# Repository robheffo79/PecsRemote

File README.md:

# PECS Remote

A Control and Administration platform for a PECS (Picture Exchange Communication System) based Remote Control system for people with ASD (Autism Spectrum Disorder) or other learning difficulties.

## Description

This software is being developed to accompany the hardware platform described at [hackaday.io](https://hackaday.io/project/166070-pecs-remote-control).
The aim is to create an integrated platform to display a pictographic representation of choices available to the user, and allow them to choose via a simple touch of the screen.
The platform needs to be reliable, rugged, simple to use, simple to administer, and secure.

## Authors

[Robert Heffernan](https://hackaday.io/RobHeffo)

## Version History

* 0.1
    * Initial Release

## License

This project is licensed under the MIT License - see the LICENSE.md file for details

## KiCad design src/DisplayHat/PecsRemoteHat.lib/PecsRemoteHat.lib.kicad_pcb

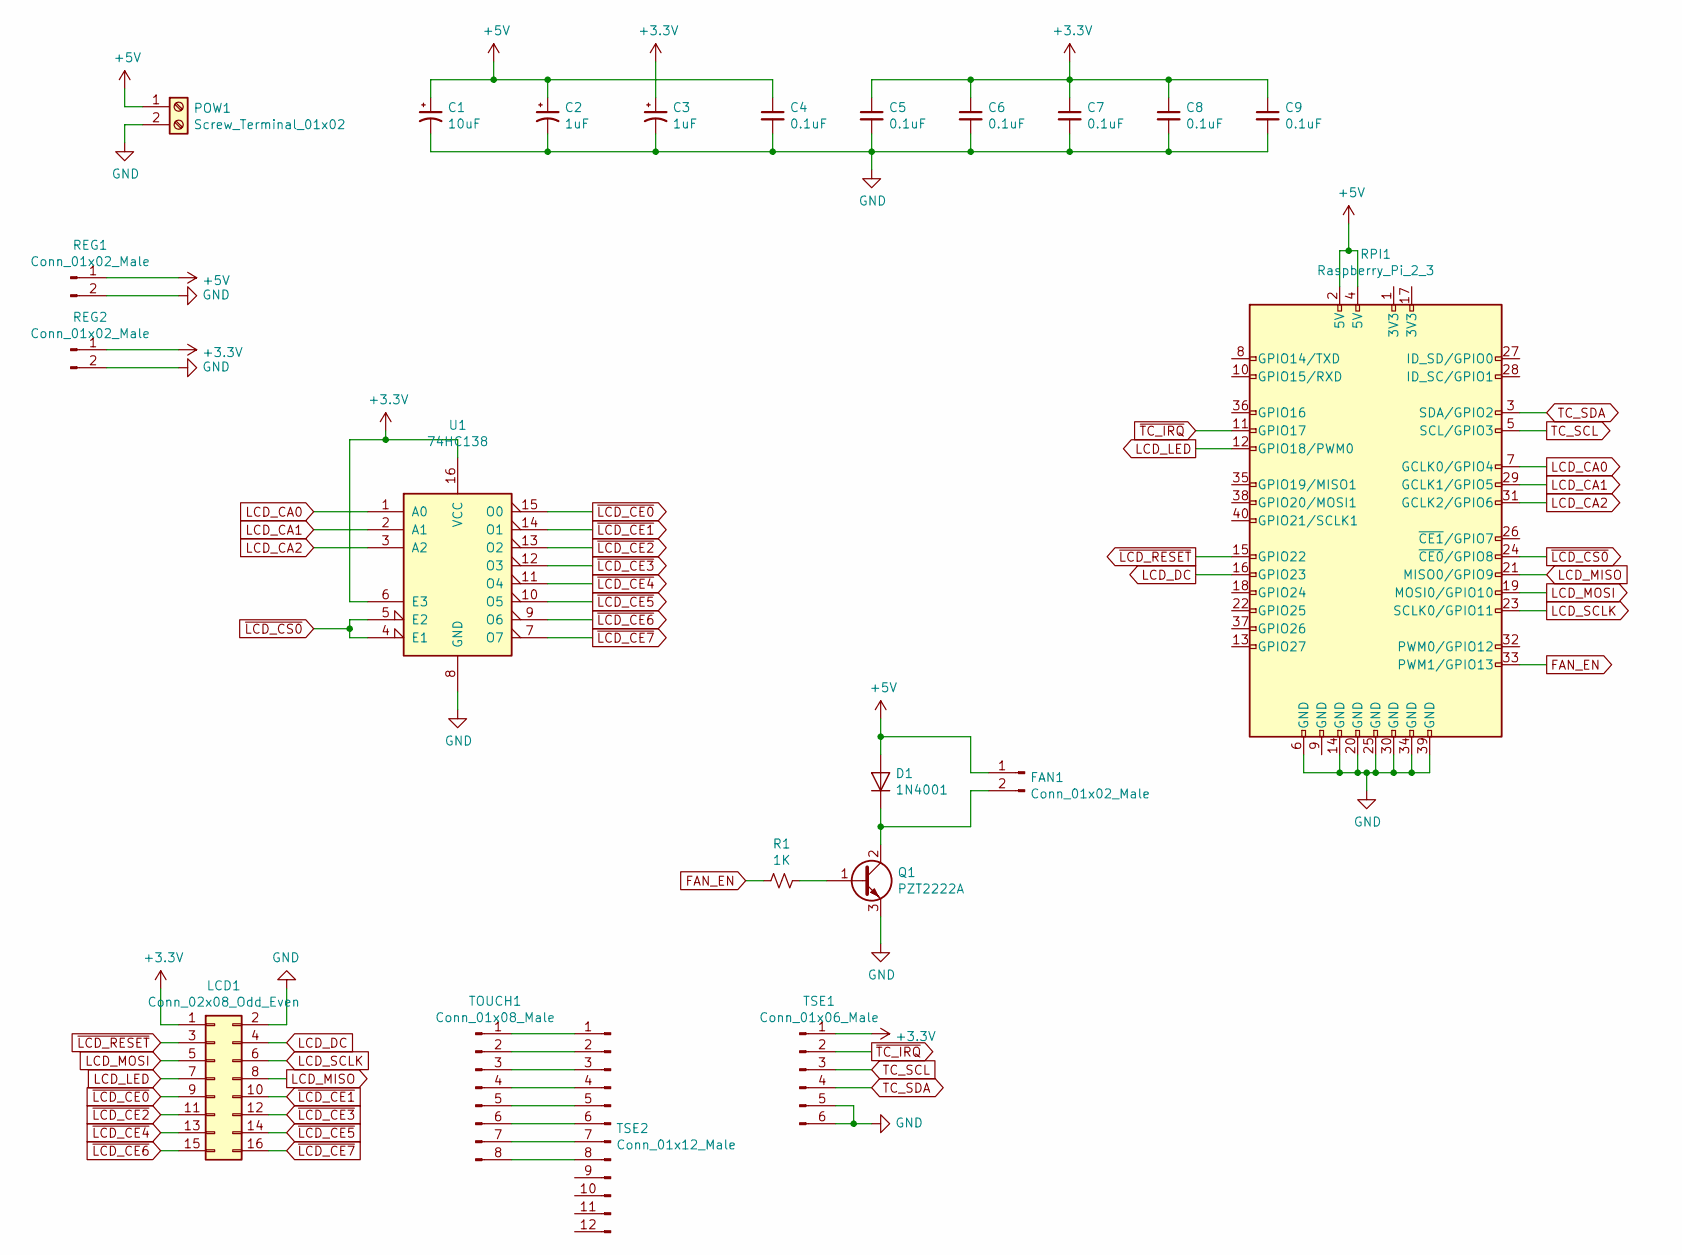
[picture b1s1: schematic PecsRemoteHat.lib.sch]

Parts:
C1: 10uF; CP_Elec_6.3x7.7
C2, C3: 1uF; CP_Elec_4x5.8
C4, C5, C6, C7, C8, C9: 0.1uF; C_1206_3216Metric_Pad1.42x1.75mm_HandSolder
D1: 1N4001; D_DO-41_SOD81_P10.16mm_Horizontal
FAN1: Conn_01x02_Male; PinHeader_1x02_P2.54mm_Vertical
LCD1: Conn_02x08_Odd_Even; IDC-Header_2x08_P2.54mm_Horizontal
POW1: Screw_Terminal_01x02; TerminalBlock_Altech_AK300-2_P5.00mm
Q1: PZT2222A; SOT-223
R1: 1K; R_1206_3216Metric_Pad1.42x1.75mm_HandSolder
REG1, REG2: Conn_01x02_Male; PinHeader_1x02_P2.54mm_Vertical
RPI1: Raspberry_Pi_2_3; PinHeader_2x20_P2.54mm_Vertical
TOUCH1: Conn_01x08_Male; PinHeader_1x08_P2.54mm_Horizontal
TSE1: Conn_01x06_Male; PinHeader_1x06_P2.54mm_Vertical
TSE2: Conn_01x12_Male; PinHeader_1x12_P2.54mm_Vertical
U1: 74HC138; SOIC-16_3.9x9.9mm_P1.27mm

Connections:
+3V3: C3.1, C5.1, C6.1, C7.1, C8.1, C9.1, LCD1.1, REG2.1, TSE1.1, U1.6 (E3), U1.16 (VCC)
+5V: C1.1, C2.1, C4.1, D1.2 (A), FAN1.1, POW1.1, REG1.1, RPI1.2 (5V), RPI1.4 (5V)
FAN_EN: R1.2, RPI1.33 (PWM1/GPIO13)
GND: C1.2, C2.2, C3.2, C4.2, C5.2, C6.2, C7.2, C8.2, C9.2, LCD1.2, POW1.2, Q1.3 (E), REG1.2, REG2.2, RPI1.6 (GND), RPI1.14 (GND), RPI1.20 (GND), RPI1.25 (GND), RPI1.30 (GND), RPI1.34 (GND), RPI1.39 (GND), TSE1.5, TSE1.6, U1.8 (GND)
LCD_CA0: RPI1.7 (GCLK0/GPIO4), U1.1 (A0)
LCD_CA1: RPI1.29 (GCLK1/GPIO5), U1.2 (A1)
LCD_CA2: RPI1.31 (GCLK2/GPIO6), U1.3 (A2)
LCD_DC: LCD1.4, RPI1.16 (GPIO23)
LCD_LED: LCD1.7, RPI1.12 (GPIO18/PWM0)
LCD_MISO: LCD1.8, RPI1.21 (MISO0/GPIO9)
LCD_MOSI: LCD1.5, RPI1.19 (MOSI0/GPIO10)
LCD_SCLK: LCD1.6, RPI1.23 (SCLK0/GPIO11)
unnamed: D1.1 (K), FAN1.2, Q1.2 (C)
unnamed: Q1.1 (B), R1.1
unnamed: TOUCH1.1, TSE2.1
unnamed: TOUCH1.2, TSE2.2
unnamed: TOUCH1.3, TSE2.3
unnamed: TOUCH1.4, TSE2.4
unnamed: TOUCH1.5, TSE2.5
unnamed: TOUCH1.6, TSE2.6
unnamed: TOUCH1.7, TSE2.7
unnamed: TOUCH1.8, TSE2.8
TC_SCL: RPI1.5 (SCL/GPIO3), TSE1.3
TC_SDA: RPI1.3 (SDA/GPIO2), TSE1.4
~LCD_CE0: LCD1.9, U1.15 (O0)
~LCD_CE1: LCD1.10, U1.14 (O1)
~LCD_CE2: LCD1.11, U1.13 (O2)
~LCD_CE3: LCD1.12, U1.12 (O3)
~LCD_CE4: LCD1.13, U1.11 (O4)
~LCD_CE5: LCD1.14, U1.10 (O5)
~LCD_CE6: LCD1.15, U1.9 (O6)
~LCD_CE7: LCD1.16, U1.7 (O7)
~LCD_CS0: RPI1.24 (~CE0~/GPIO8), U1.4 (E1), U1.5 (E2)
~LCD_RESET: LCD1.3, RPI1.15 (GPIO22)
~TC_IRQ: RPI1.11 (GPIO17), TSE1.2

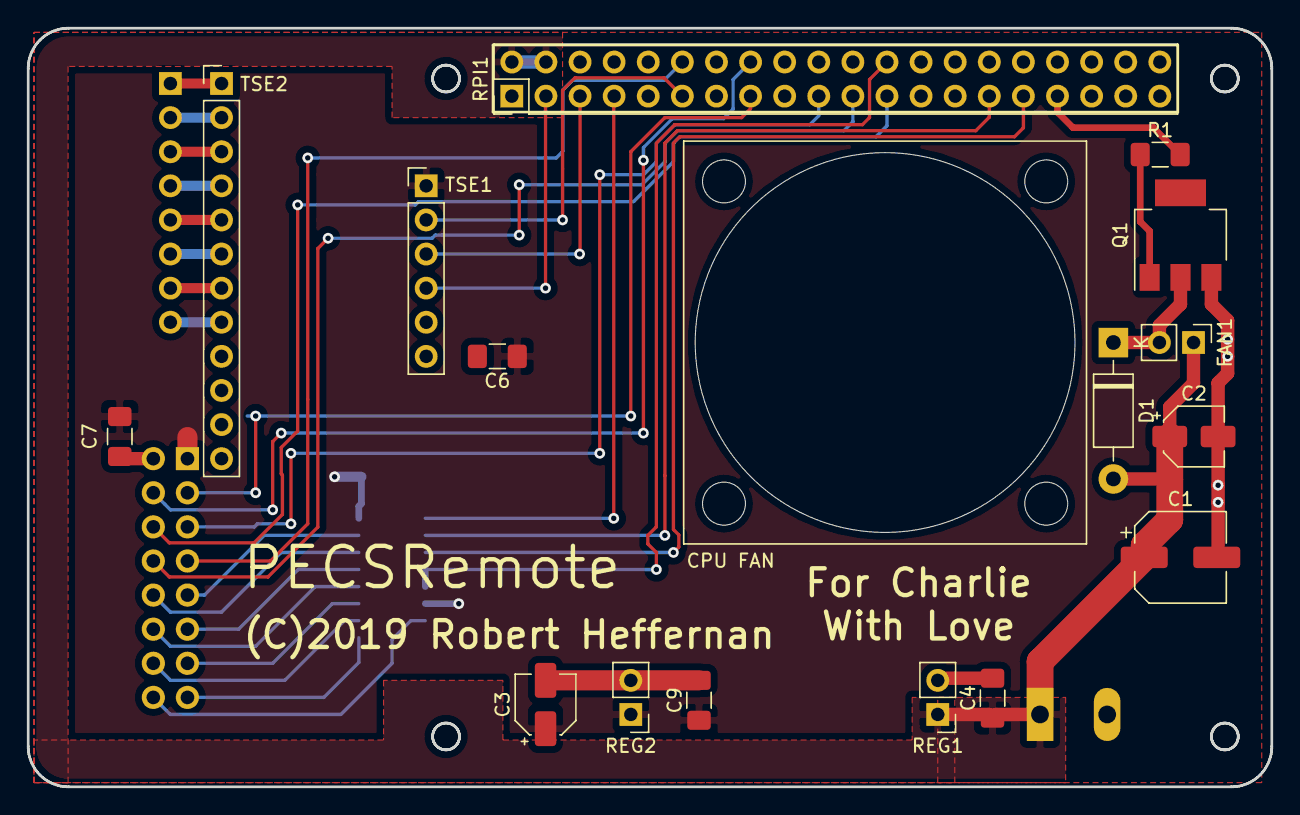
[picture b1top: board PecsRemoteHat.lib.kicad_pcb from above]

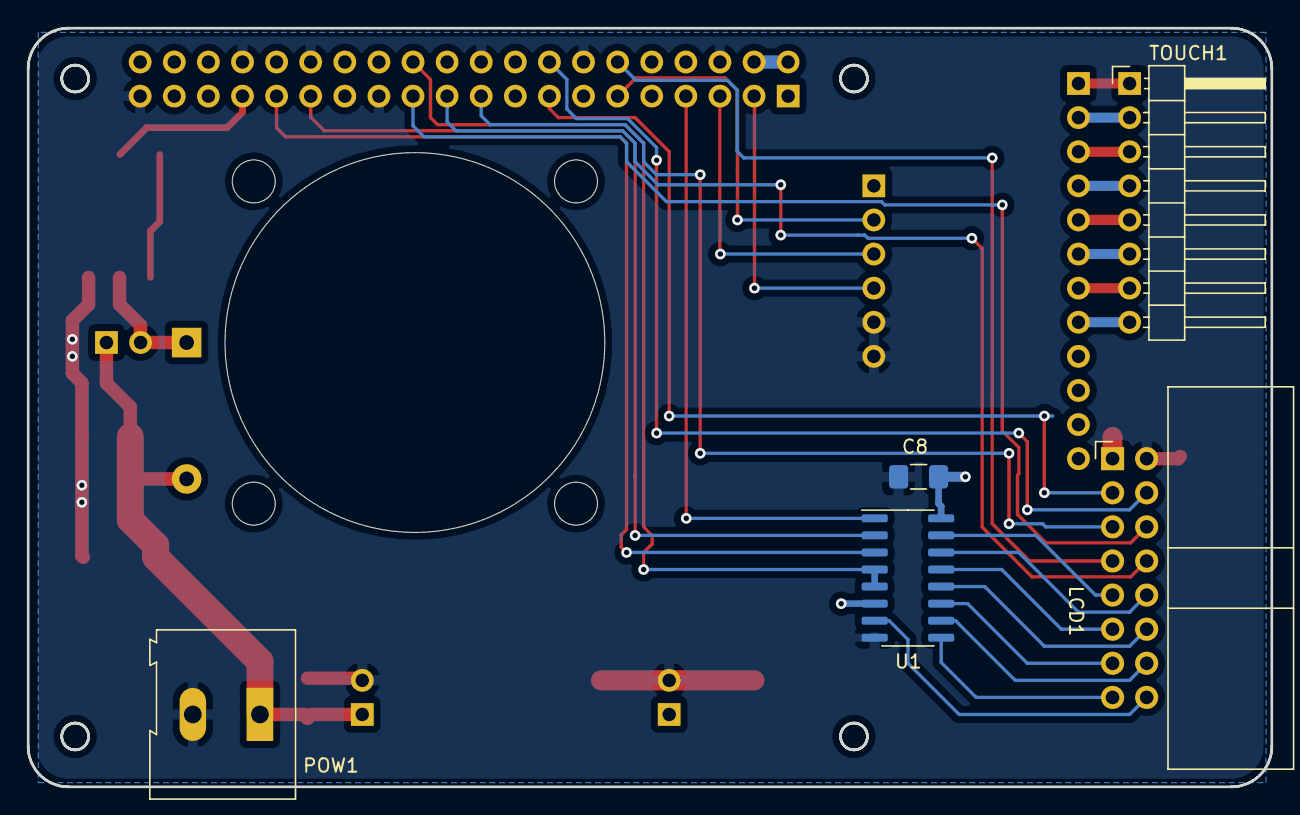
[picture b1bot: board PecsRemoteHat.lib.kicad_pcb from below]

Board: 2 copper layers, 92.6 x 56.5 mm, 21 parts (5 on the bottom side), 35 nets.

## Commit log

2019-06-15 Updated LICENSE and README files.
2019-06-15 Created empty ASP.NET Core 2.2 API
2019-06-15 Stub in the User object and User service
2019-06-15 Change IUserService to return a String (JWT) instead of a boolean
2019-06-15 Create simple MySql Data Context and Repository.
2019-06-16 Add database schema file.
2019-06-16 Add Stub Admin Website Project
2019-06-16 Add Vue.js
2019-06-17 Replace web content with own structure
2019-06-18 Made login page work
2019-06-18 Implement Authentication Pipeline in API
2019-06-19 Make Login Functionality Work
2019-06-20 Add Main Navbar. Stub in footer. Add Logout Functionality
2019-06-20 Add History Menu Item. Make 'Not Implemented' Alerts.
2019-06-20 Clean appsettings
2019-06-21 Start implementing Host interface and Raspberry Pi host specific code
2019-06-21 Added code to query for Framebuffer information and use that when outputting to displays.
2019-06-21 Add WiFi Scanning Functionality
2019-06-21 Remove appsettings
2019-06-21 Remove Files
2019-06-21 Add Reboot Host Command
2019-06-24 Add new data models and schema for playlist and media managememt
2019-06-24 Added "CurrentUser" property to UserService. Implemented AddMedia function in MediaService
2019-06-24 Implement all MediaService methods and add parameter checking.
2019-06-25 Added 'NextSalt' method to RandomService. Finished UserService implementation
2019-06-26 Add CastService
2019-06-26 Converted CastService to Async
2019-06-26 Start converting HostService methods to async
2019-06-26 Make more of HostService async
2019-06-26 Start implementing Setup page
2019-06-27 Work on update process
2019-06-28 Refine update process
2019-06-30 Casting Works
2019-06-30 Properly implemented CastController
2019-07-04 Implement EventLogService, MediaService, MediaController
2019-07-05 Implementing a lot of meaty functions
2019-07-07 Large strides in functionality
2019-07-09 Start refactoring Updates to be a Notifications system
2019-07-10 Add Security BanHammer
2019-07-10 Enabled Proxy Middleware
2019-07-11 Make Auto Database Initialisation Work
2019-07-11 Fix issue with SQL splitting where an escaped quote would break out of quoted section early
2019-07-12 Minor refactoring
2019-08-08 Bulk work. Can't list it all.
2019-08-09 Add DisplayHat Project
2019-09-21 Push many changes and PCB layout
2019-09-23 Convert constants to Database Configuration Entries

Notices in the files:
src/DisplayHat/PecsRemoteHat.lib/PecsRemoteHat.lib.kicad_pcb:
(C)2019 Robert Heffernan
